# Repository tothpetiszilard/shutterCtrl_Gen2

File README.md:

# Development of an electric window shutter motor controller
- This is the second version of my project -> First version use two SSRs, this one use one SSR (zero-cross) and one relay
- The plan is to first select the direction with the relay, then turn on the motor with the SSR
- Varistors are not optional, they are required to protect the electronics
- There will be two boards, one for the high voltage components and one for the control logic
- There is a standard shutter ctrl switch (legrand) in the wall with 3 wires, that will be also utilized and will be connected to the controller board
- Shutter motor is generic, no electronic control, only internal end-stop switches (NC)
- Whole stuff should fit into an european standard 80mm round electric box
- Optional IR led is available on the controller board to control the AC units in the rooms (experimental)

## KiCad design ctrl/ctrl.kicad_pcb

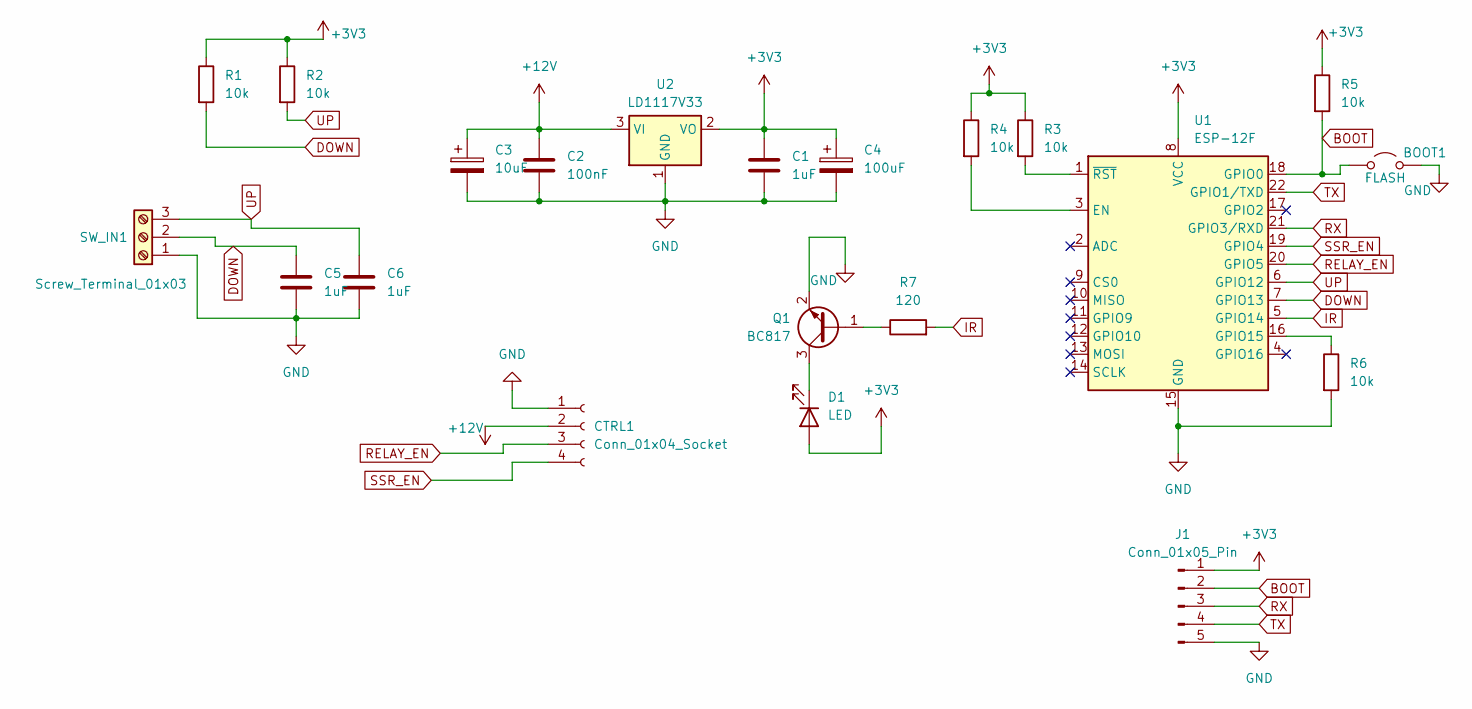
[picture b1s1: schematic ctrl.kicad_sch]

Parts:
BOOT1: FLASH; TestPoint_2Pads_Pitch2.54mm_Drill0.8mm
C1, C5, C6: 1uF; C_0603_1608Metric_Pad1.08x0.95mm_HandSolder
C2: 100nF; C_0603_1608Metric_Pad1.08x0.95mm_HandSolder
C3: 10uF; CP_Radial_Tantal_D4.5mm_P2.50mm
C4: 100uF; CP_Radial_D5.0mm_P2.00mm
CTRL1: Conn_01x04_Socket; PinHeader_1x04_P2.54mm_Vertical
D1: LED; LED_D5.0mm_Clear
J1: Conn_01x05_Pin; Molex_SL_171971-0005_1x05_P2.54mm_Vertical
Q1: BC817; SOT-23
R1, R2, R3, R4, R5, R6: 10k; R_0603_1608Metric_Pad0.98x0.95mm_HandSolder
R7: 120; R_0603_1608Metric_Pad0.98x0.95mm_HandSolder
SW_IN1: Screw_Terminal_01x03; TerminalBlock_MaiXu_MX126-5.0-03P_1x03_P5.00mm
U1: ESP-12F; ESP-12E
U2: LD1117V33; TO-220-3_Vertical

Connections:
+3V3: C1.1, C4.1, D1.2 (A), J1.1, R1.1, R2.1, R3.1, R4.1, R5.1, U1.8 (VCC), U2.2 (VO)
+12V: C2.1, C3.1, CTRL1.2, U2.3 (VI)
BOOT: BOOT1.1 (A), J1.2, R5.2, U1.18 (GPIO0)
DOWN: C5.1, R1.2, SW_IN1.2, U1.7 (GPIO13)
GND: BOOT1.2 (B), C1.2, C2.2, C3.2, C4.2, C5.2, C6.2, CTRL1.1, J1.5, Q1.2 (E), R6.2, SW_IN1.1, U1.15 (GND), U2.1 (GND)
IR: R7.2, U1.5 (GPIO14)
unnamed: D1.1 (K), Q1.3 (C)
unnamed: Q1.1 (B), R7.1
unnamed: R4.2, U1.3 (EN)
unnamed: R6.1, U1.16 (GPIO15)
unnamed: R3.2, U1.1 (~RST)
RELAY_EN: CTRL1.3, U1.20 (GPIO5)
RX: J1.3, U1.21 (GPIO3/RXD)
SSR_EN: CTRL1.4, U1.19 (GPIO4)
TX: J1.4, U1.22 (GPIO1/TXD)
UP: C6.1, R2.2, SW_IN1.3, U1.6 (GPIO12)

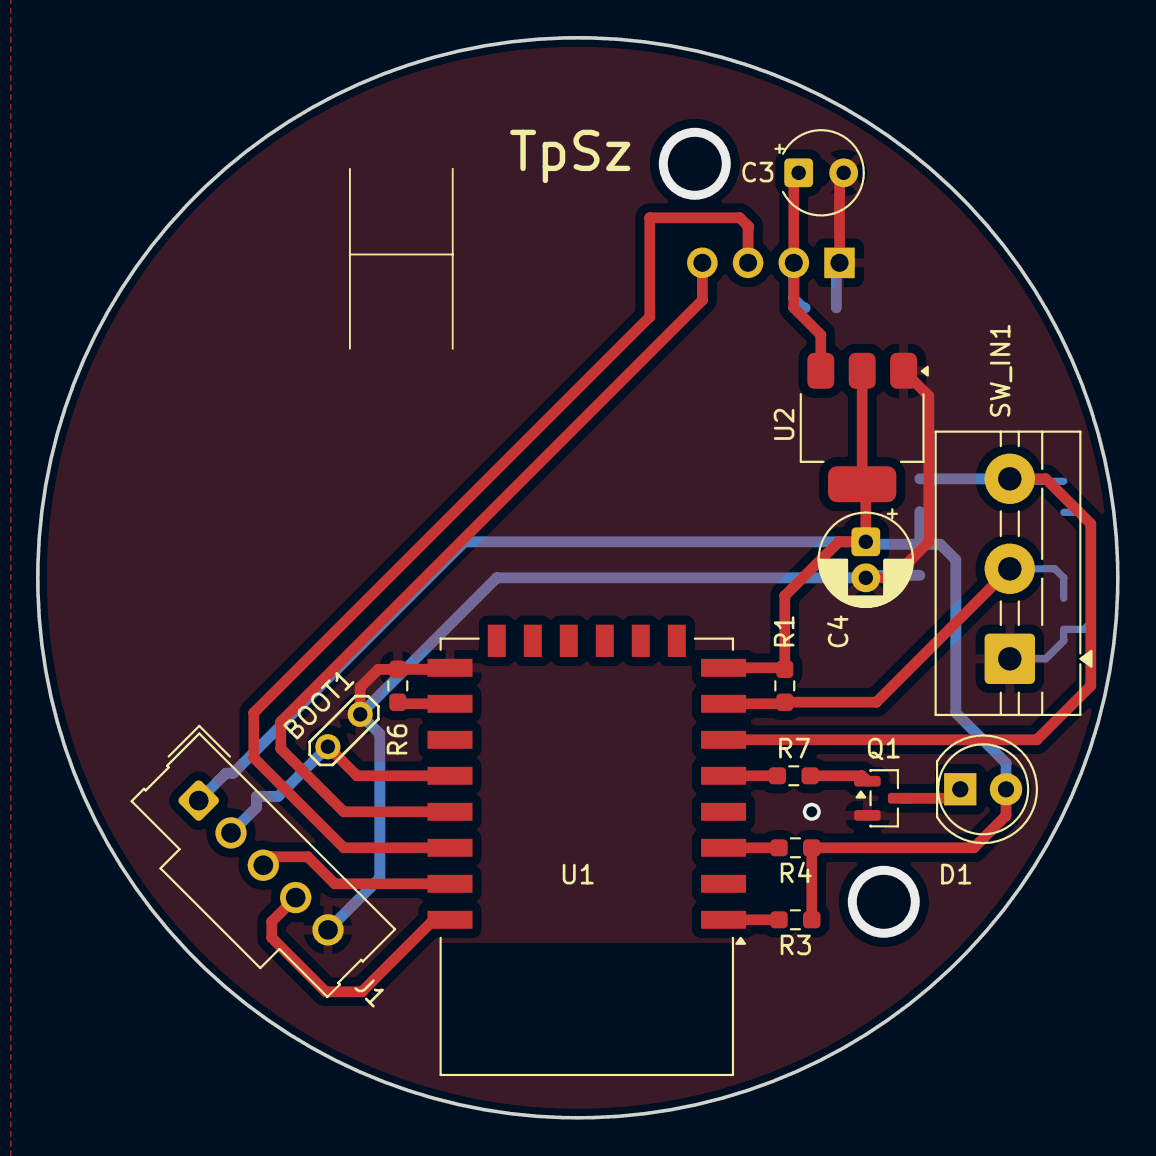
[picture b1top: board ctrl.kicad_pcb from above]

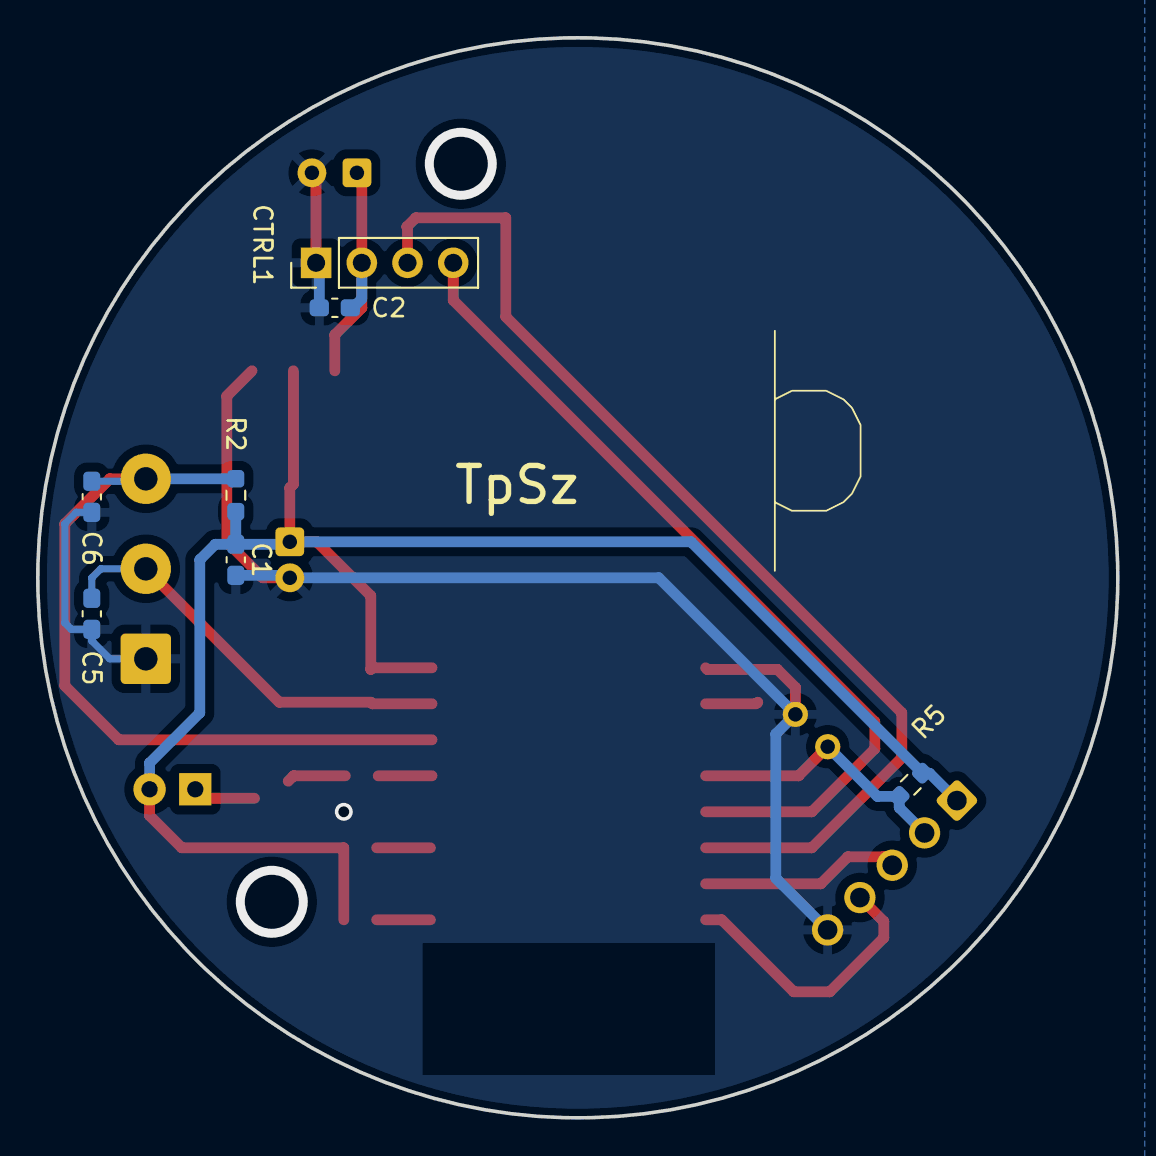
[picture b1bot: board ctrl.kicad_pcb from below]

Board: 2 copper layers, 60.0 x 60.0 mm, 21 parts (7 on the bottom side), 16 nets.

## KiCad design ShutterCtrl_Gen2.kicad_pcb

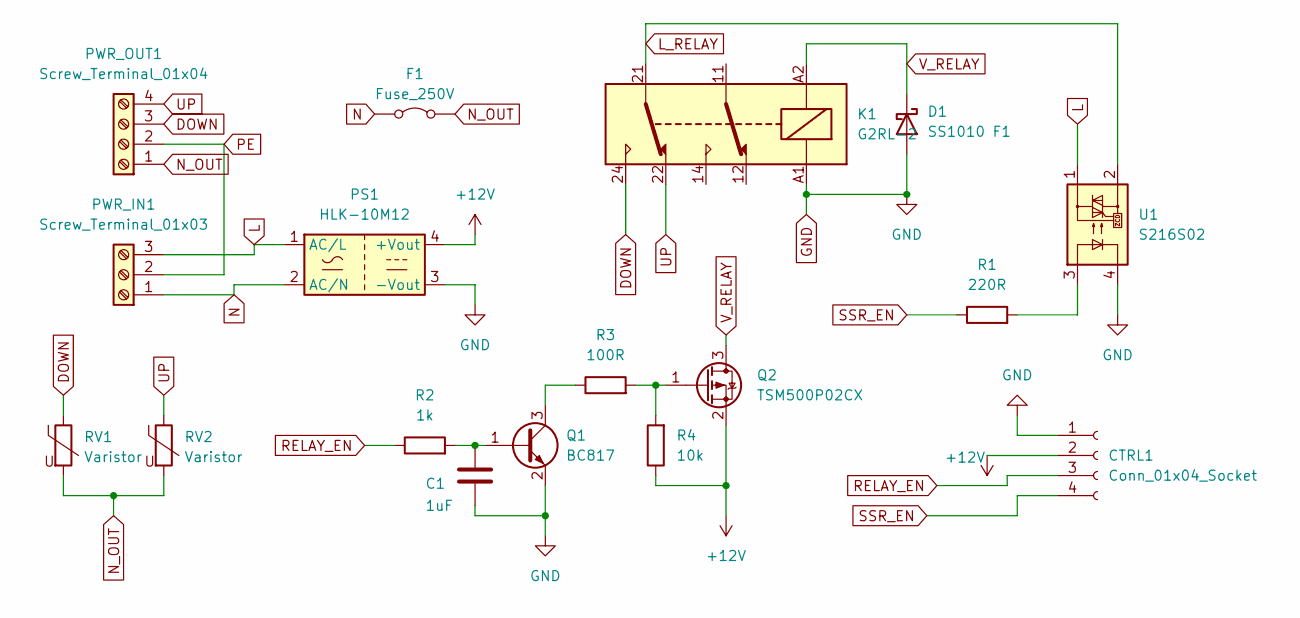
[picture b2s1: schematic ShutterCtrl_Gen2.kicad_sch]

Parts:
C1: 1uF; C_0603_1608Metric_Pad1.08x0.95mm_HandSolder
CTRL1: Conn_01x04_Socket; PinHeader_1x04_P2.54mm_Vertical
D1: SS1010 F1; D_SMC
F1: Fuse_250V; TestPoint_2Pads_Pitch5.08mm_Drill1.3mm
K1: G2RL-2; Relay_DPDT_Omron_G2RL-2
PS1: HLK-10M12; Converter_ACDC_Hi-Link_HLK-10Mxx
PWR_IN1: Screw_Terminal_01x03; TerminalBlock_MaiXu_MX126-5.0-03P_1x03_P5.00mm
PWR_OUT1: Screw_Terminal_01x04; TerminalBlock_MaiXu_MX126-5.0-04P_1x04_P5.00mm
Q1: BC817; SOT-23
Q2: TSM500P02CX; SOT-23
R1: 220R; R_0201_0603Metric_Pad0.64x0.40mm_HandSolder
R2: 1k; R_0201_0603Metric_Pad0.64x0.40mm_HandSolder
R3: 100R; R_0201_0603Metric_Pad0.64x0.40mm_HandSolder
R4: 10k; R_0201_0603Metric_Pad0.64x0.40mm_HandSolder
RV1, RV2: Varistor; RV_Disc_D12mm_W3.9mm_P7.5mm
U1: S216S02; SIP4_Sharp-SSR_P7.62mm_Straight

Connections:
+12V: CTRL1.2, PS1.4 (+Vout), Q2.2 (S), R4.1
DOWN: K1.24, PWR_OUT1.3, RV1.1
GND: C1.2, CTRL1.1, D1.2 (A), K1.A1, PS1.3 (-Vout), Q1.2 (E), U1.4
L: PS1.1 (AC/L), PWR_IN1.3, U1.1
L_RELAY: K1.21, U1.2
N: F1.1 (A), PS1.2 (AC/N), PWR_IN1.1
N_OUT: F1.2 (B), PWR_OUT1.1, RV1.2, RV2.2
unnamed: C1.1, Q1.1 (B), R2.2
unnamed: Q1.3 (C), R3.1
unnamed: Q2.1 (G), R3.2, R4.2
unnamed: R1.2, U1.3
PE: PWR_IN1.2, PWR_OUT1.2
RELAY_EN: CTRL1.3, R2.1
SSR_EN: CTRL1.4, R1.1
UP: K1.22, PWR_OUT1.4, RV2.1
V_RELAY: D1.1 (K), K1.A2, Q2.3 (D)

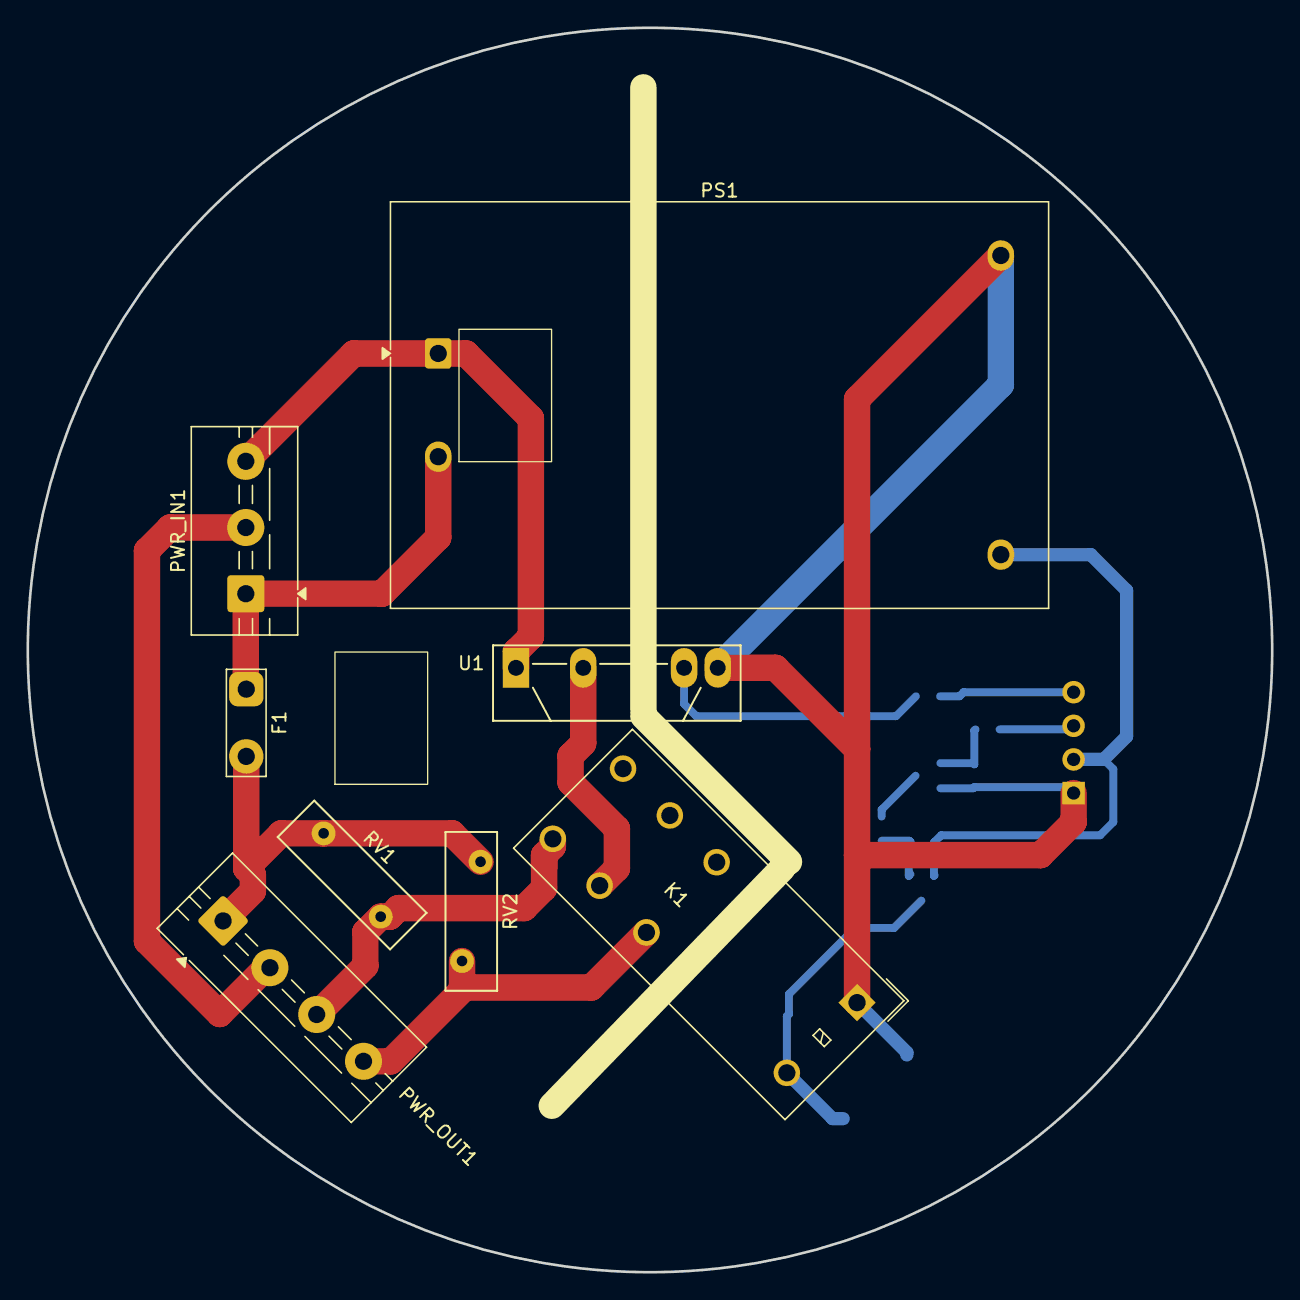
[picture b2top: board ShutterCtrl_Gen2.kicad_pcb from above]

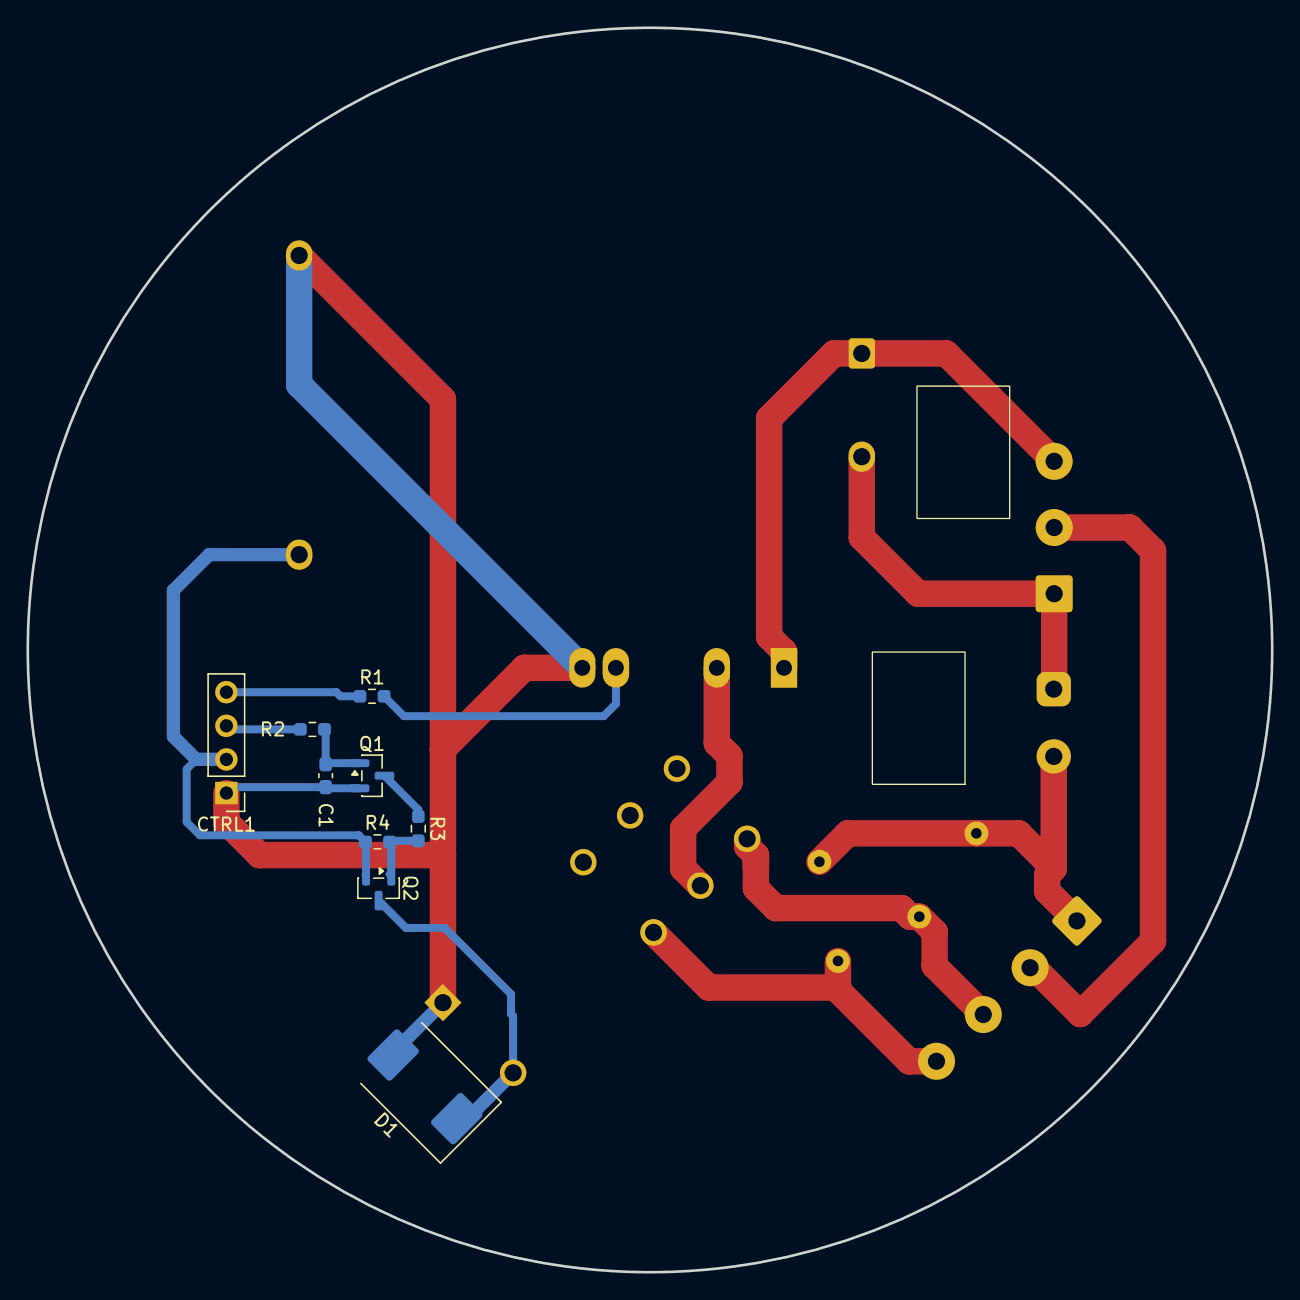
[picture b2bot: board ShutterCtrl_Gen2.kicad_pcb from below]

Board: 2 copper layers, 94.0 x 94.0 mm, 17 parts (9 on the bottom side), 16 nets.

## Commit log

2025-12-31 Initial version - PWR board designed
2025-12-31 First version of HW design
2025-12-31 Updated kicad project file
2025-12-31 PCB size was wrong, complete redesign...
2026-02-04 Pictures about the assembled power unit
